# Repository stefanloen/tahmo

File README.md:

# realtime-gnssrefl
The repository for the water level measurement system from TAHMO.

The project contains the following parts

## analysis
Provides tools for analysing GNSS date (similar to what is in the firmware).

## control
Contains the firmware for the Pico 2. For installation ensure Rust is installed and use the following commands
```bash
$ cd control
$ rustup target add thumbv8m.main-none-eabihf
```
And flash and run the firmware with the following commands:
```bash
$ cd control
$ cargo run --release
```

Creating an uf2 file:
```bash
$ picotool uf2 convert .\target\thumbv8m.main-none-eabihf\release\control -t elf control.uf2
```
## docs
Webpage tools for flashing, configuring, data viewing and documentation. Hosted at Github: [TAHMO WLM Dashboard](https://stefanloen.github.io/tahmo/)

## hardware
Contains the KiCAD PCB design files as raw project folder and as archive. Also contains some design documentation.

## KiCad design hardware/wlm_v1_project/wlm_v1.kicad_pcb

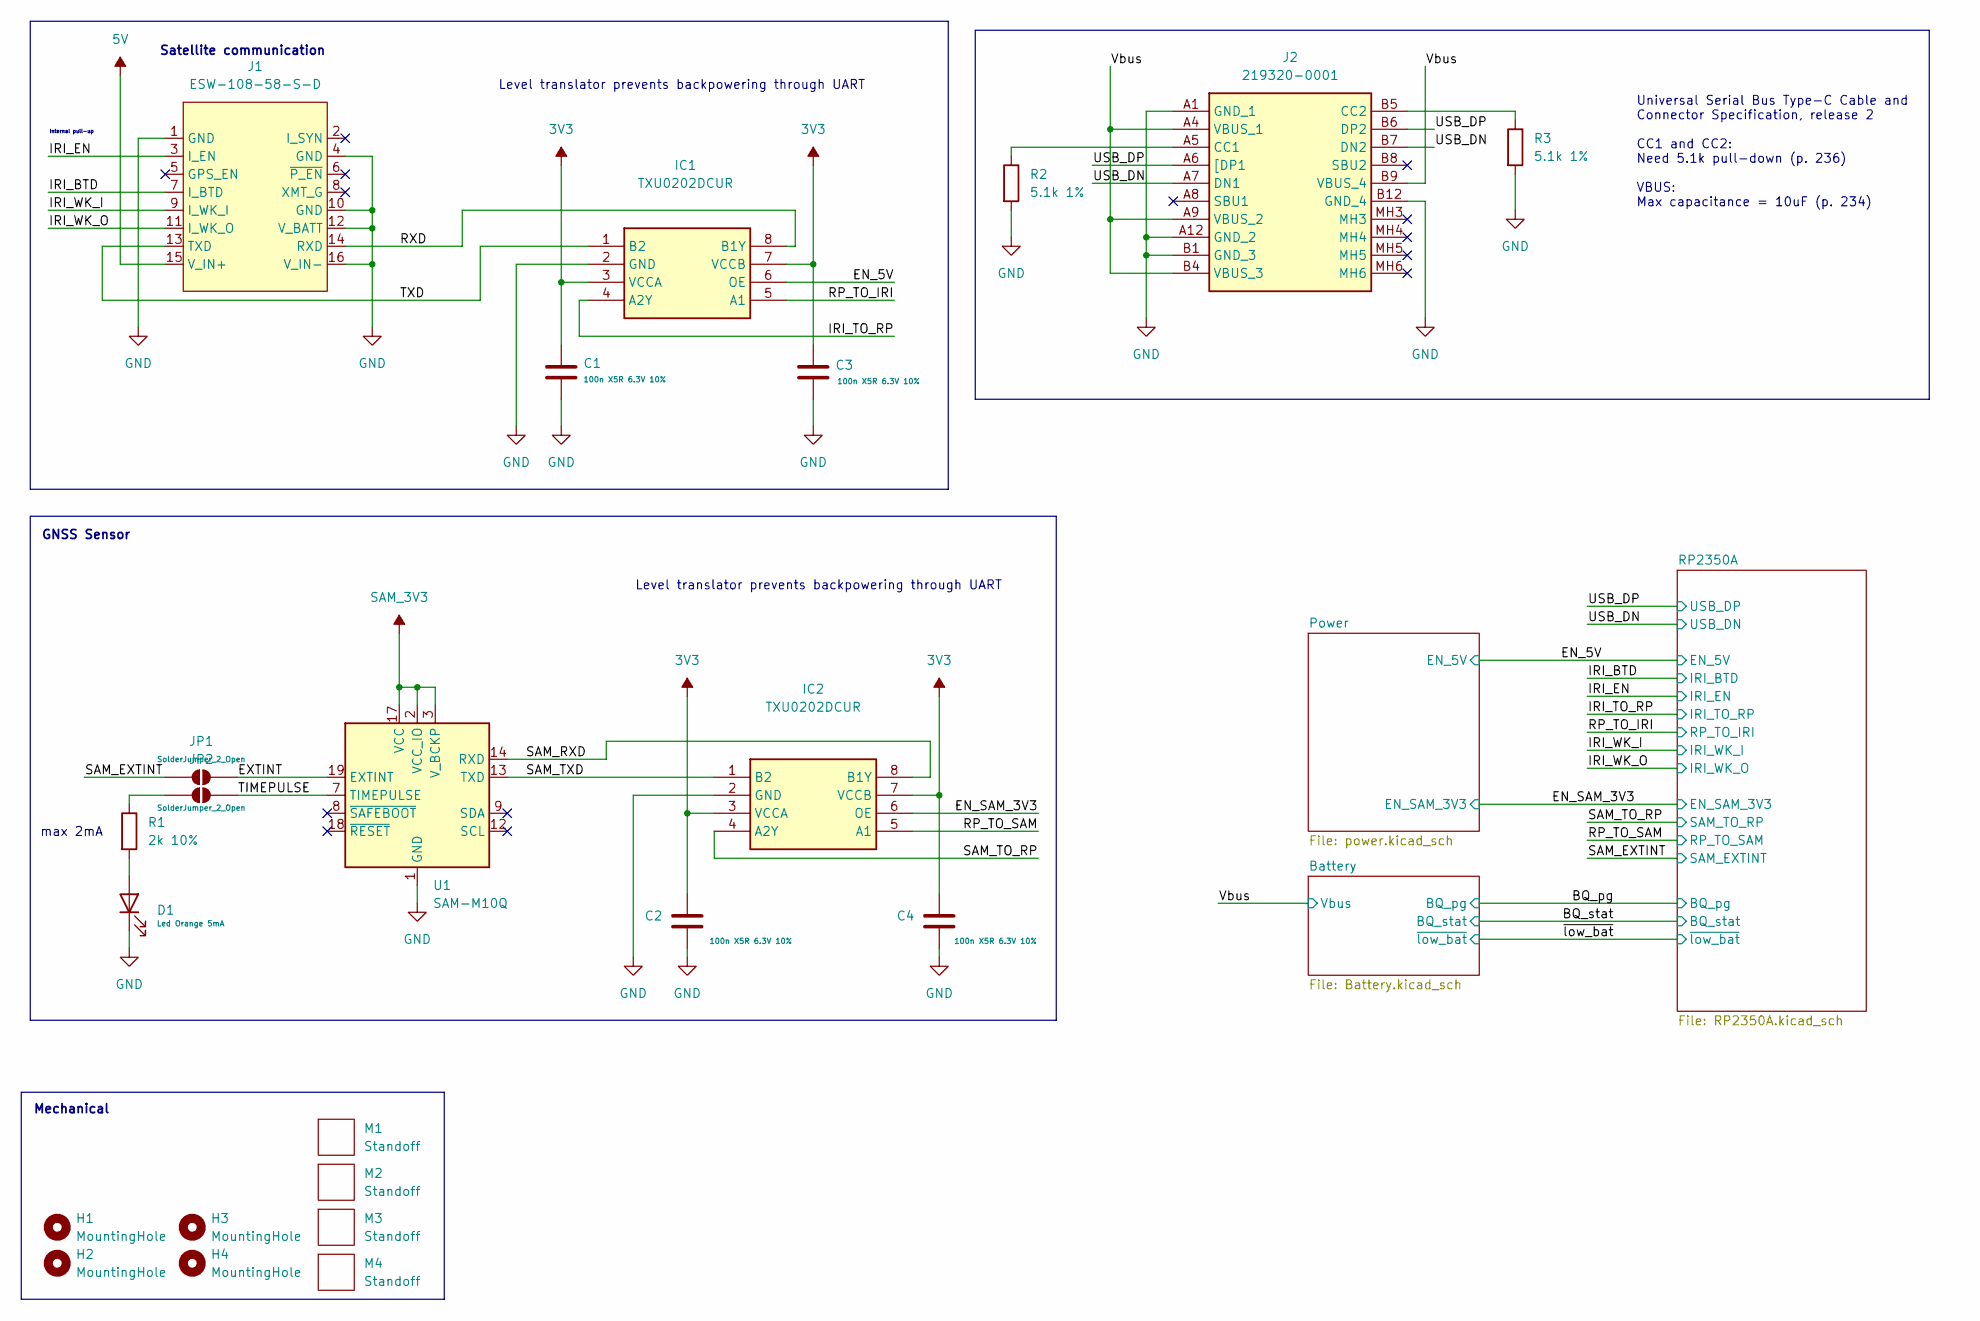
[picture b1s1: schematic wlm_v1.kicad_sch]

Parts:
C1, C2, C3, C4: 100n X5R 6.3V 10%; C_0603_1608Metric
D1: Led Orange 5mA; LED_0603_1608Metric
H1, H2, H3, H4: MountingHole; MountingHole_2.1mm
IC1, IC2: TXU0202DCUR; SOP50P310X90-8N; Mouser Part Number 595-TXU0202DCUR
J1: ESW-108-58-S-D; Rockblock_9704
J2: 219320-0001; 2193200001; Manufacturer_Part_Number 219320-0001; Mouser Part Number 538-219320-0001
JP1, JP2: SolderJumper_2_Open; SolderJumper-2_P1.3mm_Open_Pad1.0x1.5mm
M1, M2: Standoff; standoff_nohole
M3, M4: Standoff; standoff_hole
R1: 2k 10%; R_0603_1608Metric_Pad0.98x0.95mm_HandSolder
R2, R3: 5.1k 1%; R_0603_1608Metric_Pad0.98x0.95mm_HandSolder
U1: SAM-M10Q; ublox_SAM-M10Q

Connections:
3V3: C1.1, C2.1, C3.1, C4.1, IC1.3 (VCCA), IC1.7 (VCCB), IC2.3 (VCCA), IC2.7 (VCCB); also elsewhere on the board
5V: J1.15 (V_IN+); also elsewhere on the board
/EN_5V: IC1.6 (OE); also elsewhere on the board
/EN_SAM_3V3: IC2.6 (OE); also elsewhere on the board
/EXTINT: JP1.2 (B), U1.19 (EXTINT)
/IRI_BTD: J1.7 (I_BTD); also elsewhere on the board
/IRI_EN: J1.3 (I_EN); also elsewhere on the board
/IRI_TO_RP: IC1.4 (A2Y); also elsewhere on the board
/IRI_WK_I: J1.9 (I_WK_I); also elsewhere on the board
/IRI_WK_O: J1.11 (I_WK_O); also elsewhere on the board
/RP_TO_IRI: IC1.5 (A1); also elsewhere on the board
/RP_TO_SAM: IC2.5 (A1); also elsewhere on the board
/RXD: IC1.8 (B1Y), J1.14 (RXD)
/SAM_EXTINT: JP1.1 (A); also elsewhere on the board
/SAM_RXD: IC2.8 (B1Y), U1.14 (RXD)
/SAM_TO_RP: IC2.4 (A2Y); also elsewhere on the board
/SAM_TXD: IC2.1 (B2), U1.13 (TXD)
/TIMEPULSE: JP2.2 (B), U1.7 (TIMEPULSE)
/TXD: IC1.1 (B2), J1.13 (TXD)
/USB_DN: J2.A7 (DN1), J2.B7 (DN2); also elsewhere on the board
/USB_DP: J2.A6 ([DP1), J2.B6 (DP2); also elsewhere on the board
/Vbus: J2.A4 (VBUS_1), J2.A9 (VBUS_2), J2.B4 (VBUS_3), J2.B9 (VBUS_4); also elsewhere on the board
GND: C1.2, C2.2, C3.2, C4.2, D1.1 (K), IC1.2 (GND), IC2.2 (GND), J1.1 (GND), J1.4 (GND), J1.10 (GND), J1.12 (V_BATT), J1.16 (V_IN-), J2.A1 (GND_1), J2.A12 (GND_2), J2.B1 (GND_3), J2.B12 (GND_4), R2.2, R3.2, U1.1 (GND), U1.4 (GND), U1.5 (GND), U1.6 (GND), U1.10 (GND), U1.11 (GND), U1.15 (GND), U1.16 (GND), U1.20 (GND); also elsewhere on the board
unnamed: D1.2 (A), R1.2
unnamed: J2.A5 (CC1), R2.1
unnamed: J2.B5 (CC2), R3.1
unnamed: JP2.1 (A), R1.1
SAM_3V3: U1.2 (VCC_IO), U1.3 (V_BCKP), U1.17 (VCC); also elsewhere on the board

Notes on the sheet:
Internal pull-up
GNSS Sensor
Satellite communication
Mechanical
max 2mA
Universal Serial Bus Type-C Cable and Connector Specification, release 2 CC1 and CC2: Need 5.1k pull-down (p. 236) VBUS: Max capacitance = 10uF (p. 234)
Level translator prevents backpowering through UART
Level translator prevents backpowering through UART

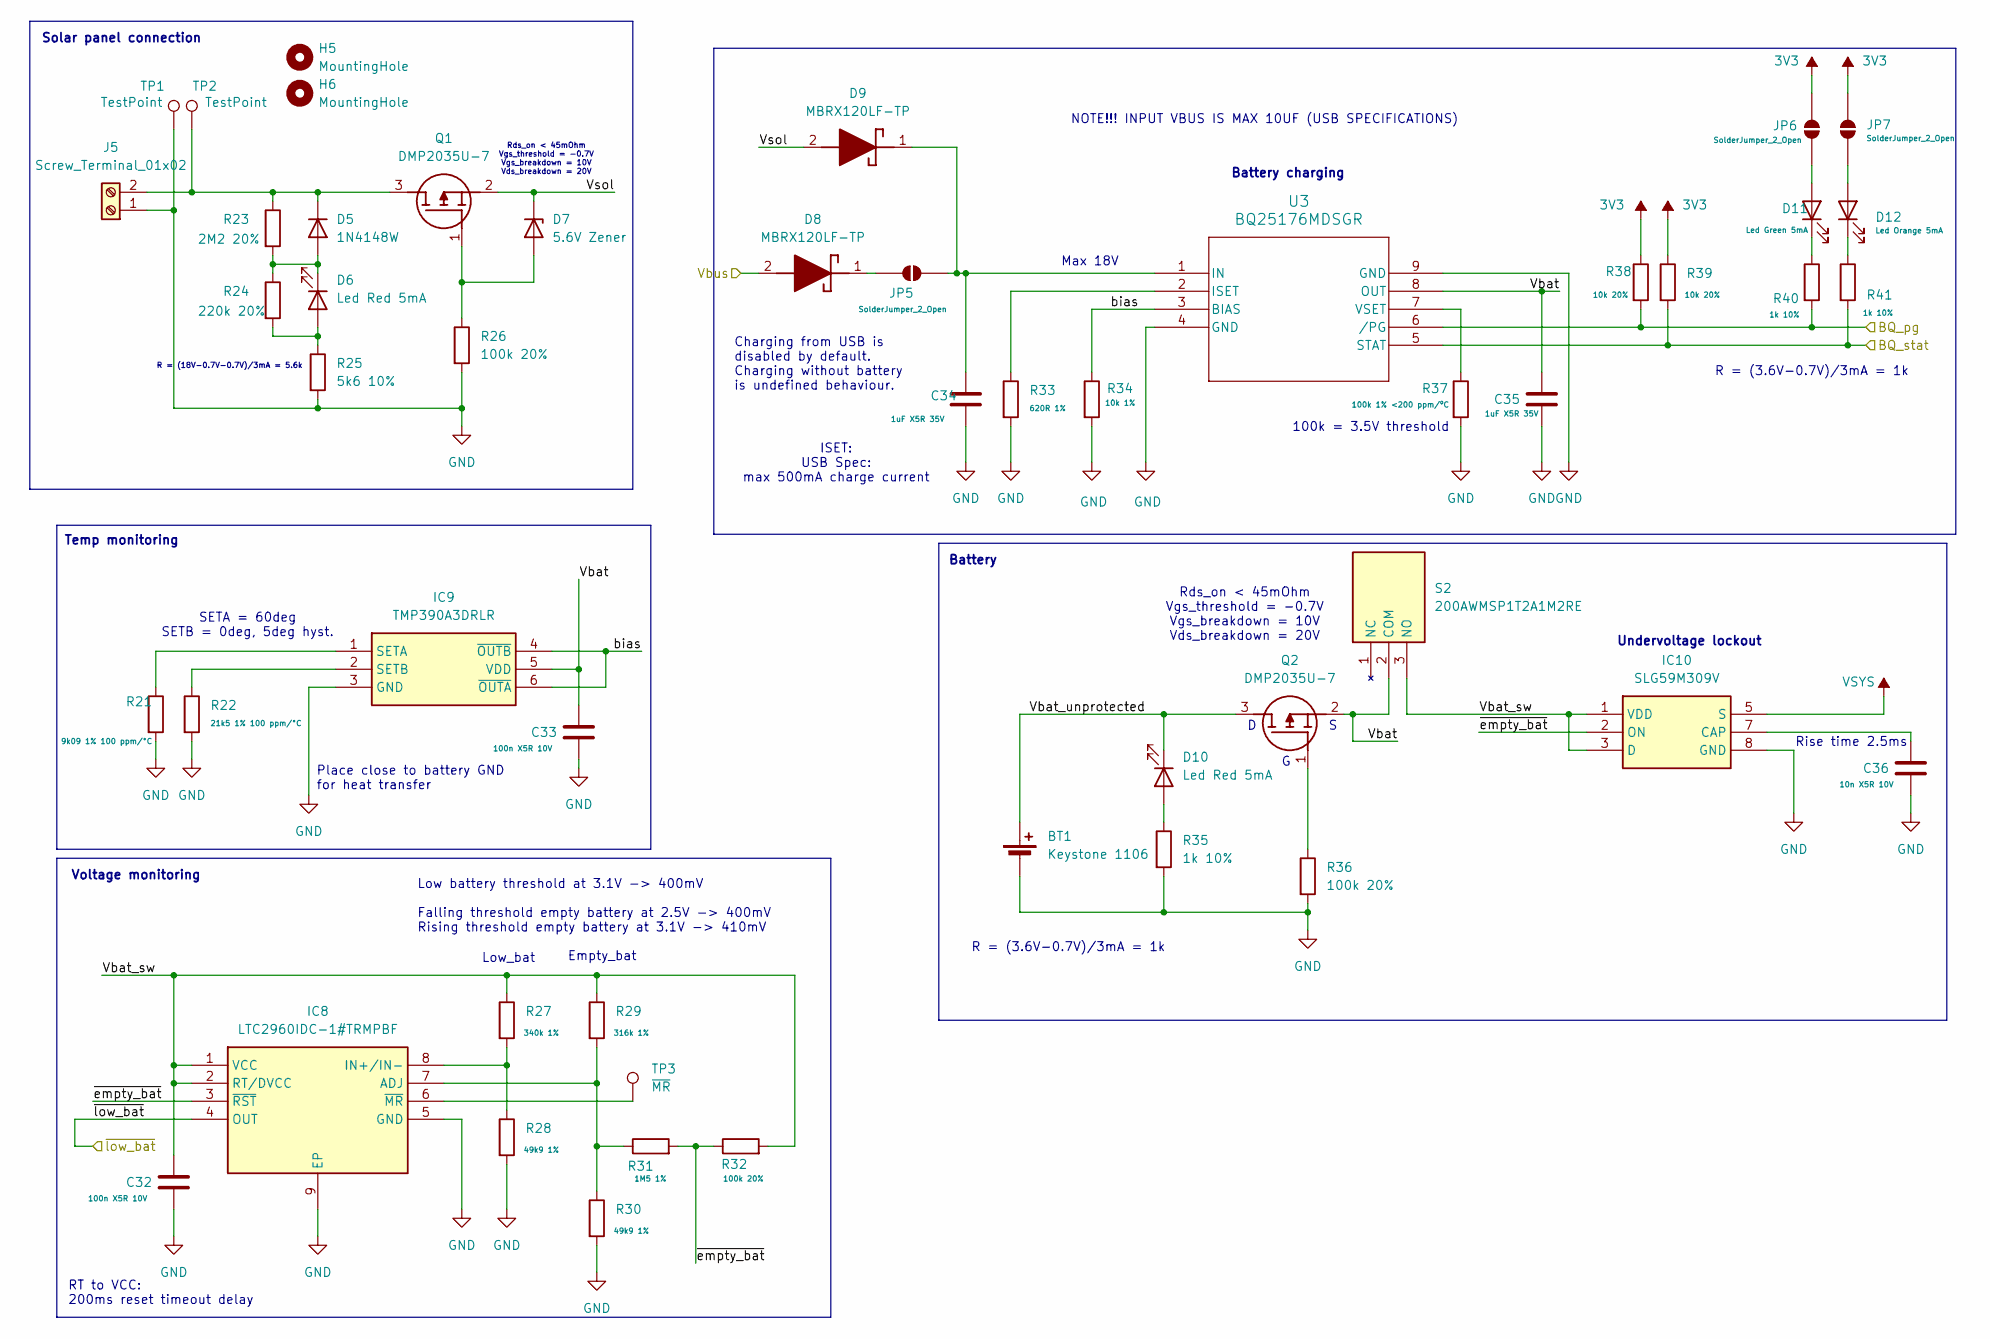
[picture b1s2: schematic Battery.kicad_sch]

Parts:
BT1: Keystone 1106; 26650_holder
C32, C33: 100n X5R 10V; C_0603_1608Metric
C34, C35: 1uF X5R 35V; C_0603_1608Metric
C36: 10n X5R 10V; C_0603_1608Metric
D5: 1N4148W; D_SOD-123
D6, D10: Led Red 5mA; LED_0603_1608Metric
D7: 5.6V Zener; D_SOD-123
D8, D9: MBRX120LF-TP; SOD3716X135N; Mouser Part Number 833-MBRX120LF-TP
D11: Led Green 5mA; LED_0603_1608Metric
D12: Led Orange 5mA; LED_0603_1608Metric
H5, H6: MountingHole; MountingHole_3.2mm_M3
IC8: LTC2960IDC-1#TRMPBF; SON45P200X200X80-9N-D; Mouser Part Number 584-C2960IDC-3TRMPBF
IC9: TMP390A3DRLR; SOTFL50P160X60-6N; Mouser Part Number 595-TMP390A3DRLR
IC10: SLG59M309V; Mouser Part Number 402-SLG59M309V
J5: Screw_Terminal_01x02; TerminalBlock_Phoenix_MKDS-1,5-2-5.08_1x02_P5.08mm_Horizont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
JP5, JP6, JP7: SolderJumper_2_Open; SolderJumper-2_P1.3mm_Open_Pad1.0x1.5mm
Q1, Q2: DMP2035U-7; DMP2035U7; Mouser Part Number 621-DMP2035U-7
R21: 9k09 1% 100 ppm/°C; R_0603_1608Metric_Pad0.98x0.95mm_HandSolder
R22: 21k5 1% 100 ppm/°C; R_0603_1608Metric_Pad0.98x0.95mm_HandSolder
R23: 2M2 20%; R_0603_1608Metric_Pad0.98x0.95mm_HandSolder
R24: 220k 20%; R_0603_1608Metric_Pad0.98x0.95mm_HandSolder
R25: 5k6 10%; R_0603_1608Metric_Pad0.98x0.95mm_HandSolder
R26, R32, R36: 100k 20%; R_0603_1608Metric_Pad0.98x0.95mm_HandSolder
R27: 340k 1%; R_0603_1608Metric_Pad0.98x0.95mm_HandSolder
R28, R30: 49k9 1%; R_0603_1608Metric_Pad0.98x0.95mm_HandSolder
R29: 316k 1%; R_0603_1608Metric_Pad0.98x0.95mm_HandSolder
R31: 1M5 1%; R_0603_1608Metric_Pad0.98x0.95mm_HandSolder
R33: 620R 1%; R_0603_1608Metric_Pad0.98x0.95mm_HandSolder
R34: 10k 1%; R_0603_1608Metric_Pad0.98x0.95mm_HandSolder
R35, R40, R41: 1k 10%; R_0603_1608Metric_Pad0.98x0.95mm_HandSolder
R37: 100k 1% <200 ppm/ºC; R_0603_1608Metric_Pad0.98x0.95mm_HandSolder
R38, R39: 10k 20%; R_0603_1608Metric_Pad0.98x0.95mm_HandSolder
S2: 200AWMSP1T2A1M2RE; Mouser Part Number 612-200A-A2162
TP1, TP2: TestPoint; TestPoint_THTPad_D2.0mm_Drill1.0mm
TP3: ~{MR}; TestPoint_Pad_D3.0mm
U3: BQ25176MDSGR; WSON_MDSGR_TEX

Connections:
3V3: JP6.2 (B), JP7.2 (B), R38.1, R39.1; also elsewhere on the board
/BQ_pg: R38.2, R40.2, U3.6 (/PG); also elsewhere on the board
/BQ_stat: R39.2, R41.2, U3.5 (STAT); also elsewhere on the board
/Battery/Vbat: C33.1, C35.1, IC9.5 (VDD), Q2.2 (S), S2.2 (COM), U3.8 (OUT)
/Battery/Vbat_sw: C32.1, IC8.1 (VCC), IC8.2 (RT/DVCC), IC10.1 (VDD), IC10.3 (D), R27.1, R29.1, R32.2, S2.3 (NO)
/Battery/Vbat_unprotected: BT1.1 (+), D10.1 (K), Q2.3 (D)
/Battery/Vsol: D7.1 (K), D9.2 (A), Q1.2 (S)
/Battery/bias: IC9.4 (~OUTB), IC9.6 (~OUTA), R34.1, U3.3 (BIAS)
/Battery/~empty_bat: IC8.3 (~RST), IC10.2 (ON), R31.2, R32.1
/Vbus: D8.2 (A); also elsewhere on the board
/~low_bat: IC8.4 (OUT); also elsewhere on the board
GND: BT1.2 (-), C32.2, C33.2, C34.2, C35.2, C36.2, IC8.5 (GND), IC8.9 (EP), IC9.3 (GND), IC10.8 (GND), J5.1, R21.2, R22.2, R25.2, R26.2, R28.2, R30.2, R33.2, R34.2, R35.2, R36.2, R37.2, TP1.1 (1_1), U3.4 (GND), U3.9 (GND); also elsewhere on the board
unnamed: D5.2 (A), D6.1 (K), R23.2, R24.1
unnamed: D5.1 (K), J5.2, Q1.3 (D), R23.1, TP2.1 (1_1)
unnamed: D6.2 (A), R24.2, R25.1
unnamed: D7.2 (A), Q1.1 (G), R26.1
unnamed: D8.1 (K), JP5.2 (B)
unnamed: C34.1, D9.1 (K), JP5.1 (A), U3.1 (IN)
unnamed: D10.2 (A), R35.1
unnamed: D11.2 (A), JP6.1 (A)
unnamed: D11.1 (K), R40.1
unnamed: D12.2 (A), JP7.1 (A)
unnamed: D12.1 (K), R41.1
unnamed: IC8.7 (ADJ), R29.2, R30.1, R31.1
unnamed: IC8.8 (IN+/IN-), R27.2, R28.1
unnamed: IC8.6 (~MR), TP3.1 (1_1)
unnamed: IC9.1 (SETA), R21.1
unnamed: IC9.2 (SETB), R22.1
unnamed: C36.1, IC10.7 (CAP)
unnamed: Q2.1 (G), R36.1
unnamed: R33.1, U3.2 (ISET)
unnamed: R37.1, U3.7 (VSET)
VSYS: IC10.5 (S); also elsewhere on the board

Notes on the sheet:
Voltage monitoring
Battery
Empty_bat
SETA = 60deg SETB = 0deg, 5deg hyst.
Place close to battery GND for heat transfer
ISET: USB Spec: max 500mA charge current
Max 18V
Rds_on < 45mOhm Vgs_threshold = -0.7V Vgs_breakdown = 10V Vds_breakdown = 20V
RT to VCC: 200ms reset timeout delay
R = (18V-0.7V-0.7V)/3mA = 5.6k
R = (3.6V-0.7V)/3mA = 1k
Temp monitoring
100k = 3.5V threshold
Solar panel connection
Low battery threshold at 3.1V -> 400mV Falling threshold empty battery at 2.5V -> 400mV Rising threshold empty battery at 3.1V -> 410mV
Charging from USB is disabled by default. Charging without battery is undefined behaviour.
Battery charging
Low_bat
Undervoltage lockout
Rise time 2.5ms
NOTE!!! INPUT VBUS IS MAX 10UF (USB SPECIFICATIONS)

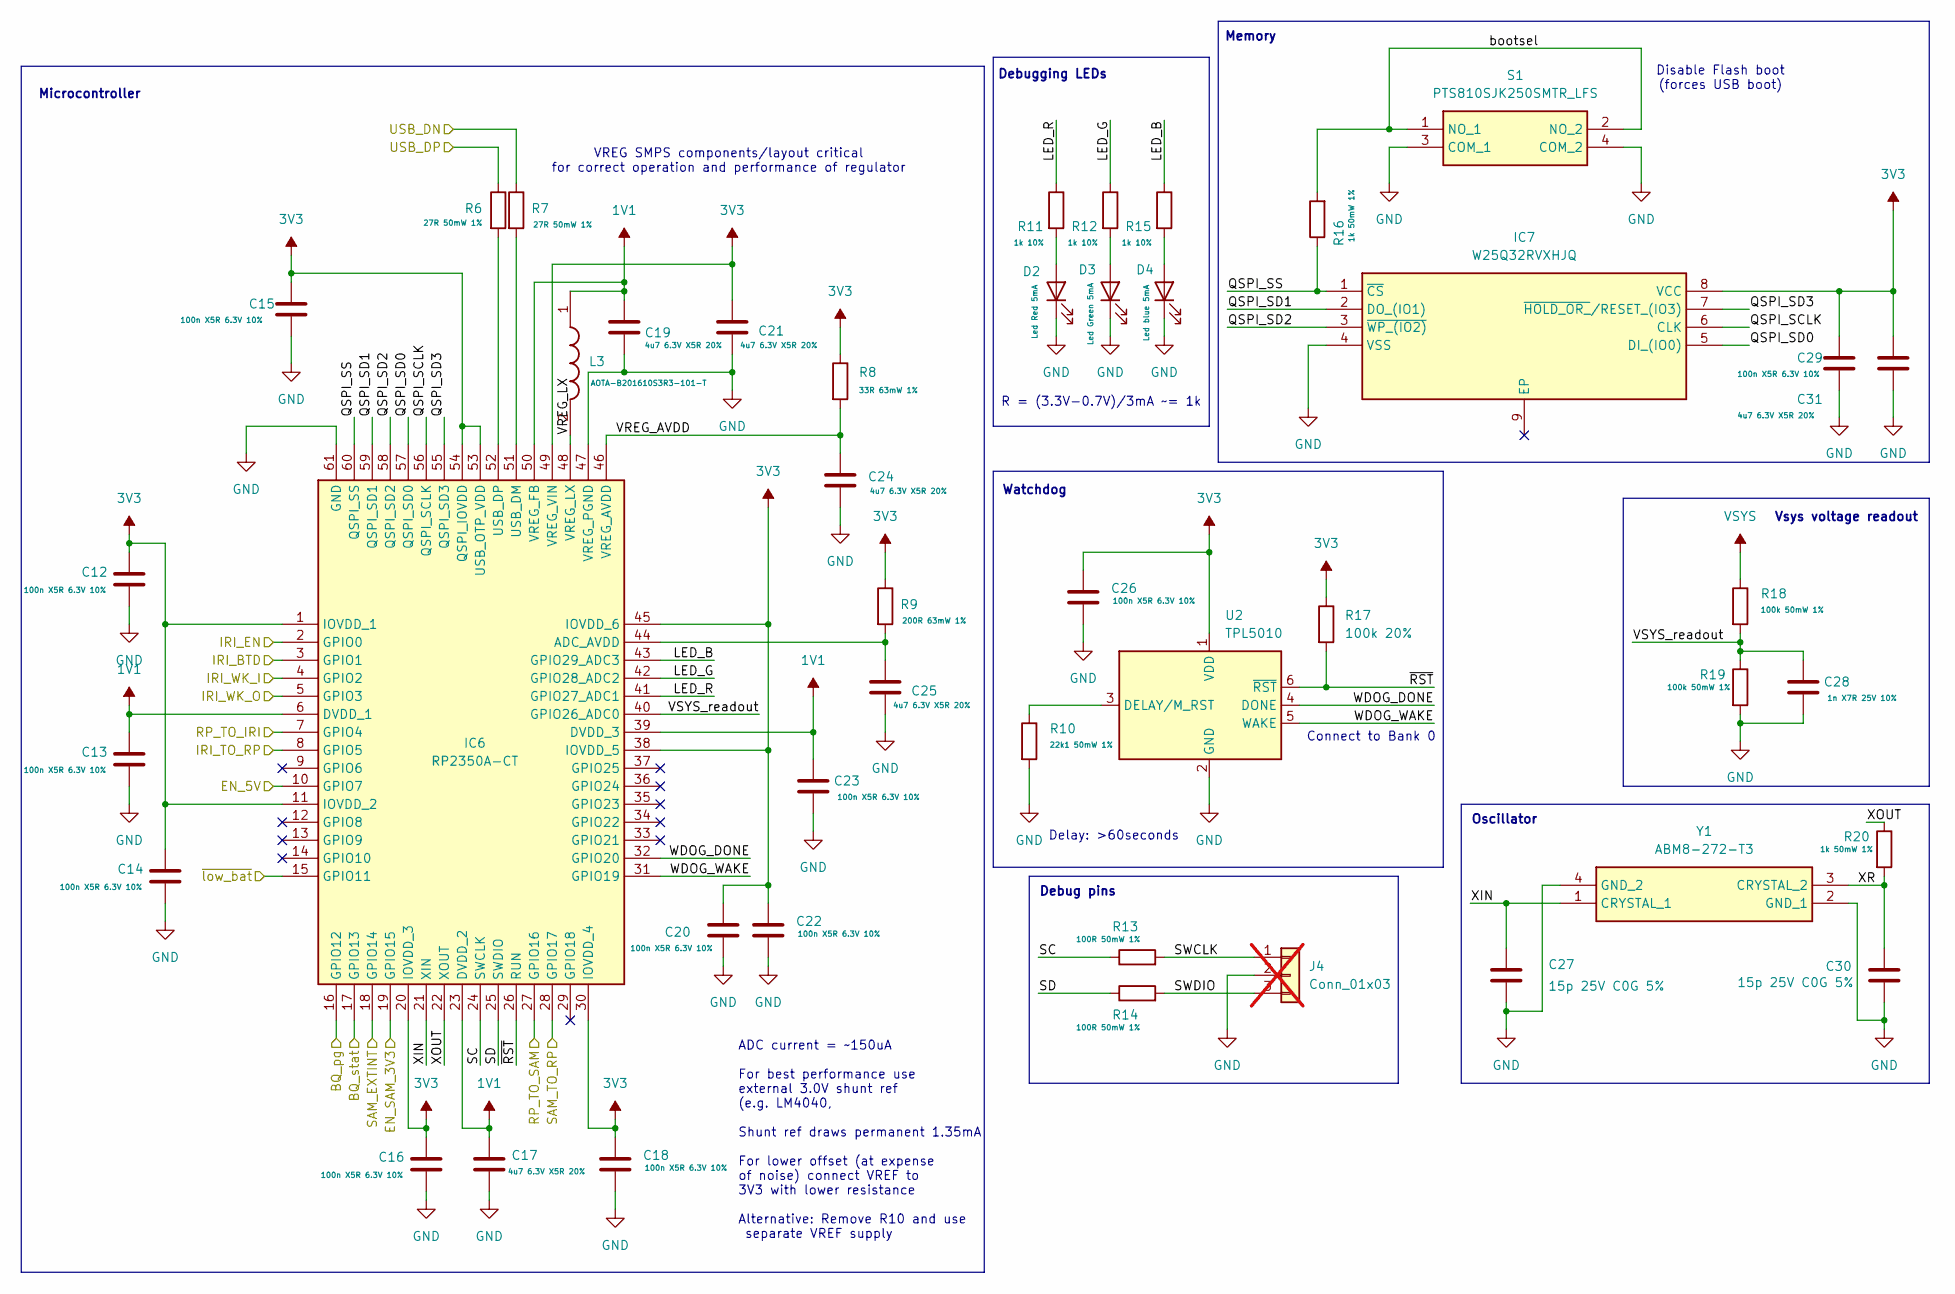
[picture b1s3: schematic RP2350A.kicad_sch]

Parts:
C12, C13, C14, C15, C16, C18, C20, C22, C23, C26, C29: 100n X5R 6.3V 10%; C_0603_1608Metric
C17, C25, C31: 4u7 6.3V X5R 20%; C_0603_1608Metric
C19, C21, C24: 4u7 6.3V X5R 20%; C_0402_1005Metric
C27, C30: 15p 25V C0G 5%; C_0603_1608Metric
C28: 1n X7R 25V 10%; C_0603_1608Metric
D2: Led Red 5mA; LED_0603_1608Metric
D3: Led Green 5mA; LED_0603_1608Metric
D4: Led blue 5mA; LED_0603_1608Metric
IC6: RP2350A-CT; QFN40P700X700X90-61N-D; Manufacturer_Part_Number RP2350A-CT
IC7: W25Q32RVXHJQ; SON50P300X200X40-9N; Manufacturer_Part_Number W25Q32RVXHJQ
J4: Conn_01x03; PinHeader_1x03_P2.54mm_Vertical; not fitted
L3: AOTA-B201610S3R3-101-T; AOTAB201610S3R3101T; Mouser Part Number 815-AB201610S3R3101T
R6, R7: 27R 50mW 1%; R_0603_1608Metric_Pad0.98x0.95mm_HandSolder
R8: 33R 63mW 1%; R_0402_1005Metric_Pad0.72x0.64mm_HandSolder
R9: 200R 63mW 1%; R_0603_1608Metric_Pad0.98x0.95mm_HandSolder
R10: 22k1 50mW 1%; R_0603_1608Metric_Pad0.98x0.95mm_HandSolder
R11, R12, R15: 1k 10%; R_0603_1608Metric_Pad0.98x0.95mm_HandSolder
R13, R14: 100R 50mW 1%; R_0603_1608Metric_Pad0.98x0.95mm_HandSolder
R16, R20: 1k 50mW 1%; R_0603_1608Metric_Pad0.98x0.95mm_HandSolder
R17: 100k 20%; R_0603_1608Metric_Pad0.98x0.95mm_HandSolder
R18, R19: 100k 50mW 1%; R_0603_1608Metric_Pad0.98x0.95mm_HandSolder
S1: PTS810SJK250SMTR_LFS; PTS810SJK250SMTRLFS; Mouser Part Number 611-PTS810SJK250SMTR
U2: TPL5010; SOT-23-6
Y1: ABM8-272-T3; ABM8272T3; Mouser Part Number 815-ABM8-272-T3

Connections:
1V1: C13.1, C17.1, C19.1, C23.1, IC6.6 (DVDD_1), IC6.23 (DVDD_2), IC6.39 (DVDD_3), IC6.50 (VREG_FB), L3.1
3V3: C12.1, C14.1, C15.1, C16.1, C18.1, C20.1, C21.1, C22.1, C26.1, C29.1, C31.1, IC6.1 (IOVDD_1), IC6.11 (IOVDD_2), IC6.20 (IOVDD_3), IC6.30 (IOVDD_4), IC6.38 (IOVDD_5), IC6.45 (IOVDD_6), IC6.49 (VREG_VIN), IC6.53 (USB_OTP_VDD), IC6.54 (QSPI_IOVDD), IC7.8 (VCC), R8.1, R9.1, R17.1, U2.1 (VDD); also elsewhere on the board
/BQ_pg: IC6.16 (GPIO12); also elsewhere on the board
/BQ_stat: IC6.17 (GPIO13); also elsewhere on the board
/EN_5V: IC6.10 (GPIO7); also elsewhere on the board
/EN_SAM_3V3: IC6.19 (GPIO15); also elsewhere on the board
/IRI_BTD: IC6.3 (GPIO1); also elsewhere on the board
/IRI_EN: IC6.2 (GPIO0); also elsewhere on the board
/IRI_TO_RP: IC6.8 (GPIO5); also elsewhere on the board
/IRI_WK_I: IC6.4 (GPIO2); also elsewhere on the board
/IRI_WK_O: IC6.5 (GPIO3); also elsewhere on the board
/RP2350A/LED_B: IC6.43 (GPIO29_ADC3), R15.1
/RP2350A/LED_G: IC6.42 (GPIO28_ADC2), R12.1
/RP2350A/LED_R: IC6.41 (GPIO27_ADC1), R11.1
/RP2350A/QSPI_SCLK: IC6.56 (QSPI_SCLK), IC7.6 (CLK)
/RP2350A/QSPI_SD0: IC6.57 (QSPI_SD0), IC7.5 (DI_(IO0))
/RP2350A/QSPI_SD1: IC6.59 (QSPI_SD1), IC7.2 (DO_(IO1))
/RP2350A/QSPI_SD2: IC6.58 (QSPI_SD2), IC7.3 (~WP_(IO2))
/RP2350A/QSPI_SD3: IC6.55 (QSPI_SD3), IC7.7 (~HOLD_OR_/RESET_(IO3))
/RP2350A/QSPI_SS: IC6.60 (QSPI_SS), IC7.1 (~CS), R16.1
/RP2350A/SC: IC6.24 (SWCLK), R13.1
/RP2350A/SD: IC6.25 (SWDIO), R14.1
/RP2350A/SWCLK: J4.1, R13.2
/RP2350A/SWDIO: J4.3, R14.2
/RP2350A/VREG_AVDD: C24.1, IC6.46 (VREG_AVDD), R8.2
/RP2350A/VREG_LX: IC6.48 (VREG_LX), L3.2
/RP2350A/VSYS_readout: C28.1, IC6.40 (GPIO26_ADC0), R18.2, R19.1
/RP2350A/WDOG_DONE: IC6.32 (GPIO20), U2.4 (DONE)
/RP2350A/WDOG_WAKE: IC6.31 (GPIO19), U2.5 (WAKE)
/RP2350A/XIN: C27.1, IC6.21 (XIN), Y1.1 (CRYSTAL_1)
/RP2350A/XOUT: IC6.22 (XOUT), R20.1
/RP2350A/XR: C30.1, R20.2, Y1.3 (CRYSTAL_2)
/RP2350A/bootsel: R16.2, S1.1 (NO_1), S1.2 (NO_2)
/RP2350A/~RST: IC6.26 (RUN), R17.2, U2.6 (~RST)
/RP_TO_IRI: IC6.7 (GPIO4); also elsewhere on the board
/RP_TO_SAM: IC6.27 (GPIO16); also elsewhere on the board
/SAM_EXTINT: IC6.18 (GPIO14); also elsewhere on the board
/SAM_TO_RP: IC6.28 (GPIO17); also elsewhere on the board
/USB_DN: R7.1; also elsewhere on the board
/USB_DP: R6.1; also elsewhere on the board
/~low_bat: IC6.15 (GPIO11); also elsewhere on the board
GND: C12.2, C13.2, C14.2, C15.2, C16.2, C17.2, C18.2, C19.2, C20.2, C21.2, C22.2, C23.2, C24.2, C25.2, C26.2, C27.2, C28.2, C29.2, C30.2, C31.2, D2.1 (K), D3.1 (K), D4.1 (K), IC6.47 (VREG_PGND), IC6.61 (GND), IC7.4 (VSS), J4.2, R10.2, R19.2, S1.3 (COM_1), S1.4 (COM_2), U2.2 (GND), Y1.2 (GND_1), Y1.4 (GND_2); also elsewhere on the board
unnamed: D2.2 (A), R11.2
unnamed: D3.2 (A), R12.2
unnamed: D4.2 (A), R15.2
unnamed: C25.1, IC6.44 (ADC_AVDD), R9.2
unnamed: IC6.51 (USB_DM), R7.2
unnamed: IC6.52 (USB_DP), R6.2
unnamed: R10.1, U2.3 (DELAY/M_RST)
VSYS: R18.1; also elsewhere on the board

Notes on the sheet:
Delay: >60seconds
Watchdog
Disable Flash boot (forces USB boot)
Vsys voltage readout
Debug pins
Debugging LEDs
VREG SMPS components/layout critical for correct operation and performance of regulator
Microcontroller
Memory
Oscillator
ADC current = ~150uA For best performance use external 3.0V shunt ref (e.g. LM4040, Shunt ref draws permanent 1.35mA For lower offset (at expense of noise) connect VREF to 3V3 with lower resistance Alternative: Remove R10 and use separate VREF supply
Connect to Bank 0
R = (3.3V-0.7V)/3mA ~= 1k

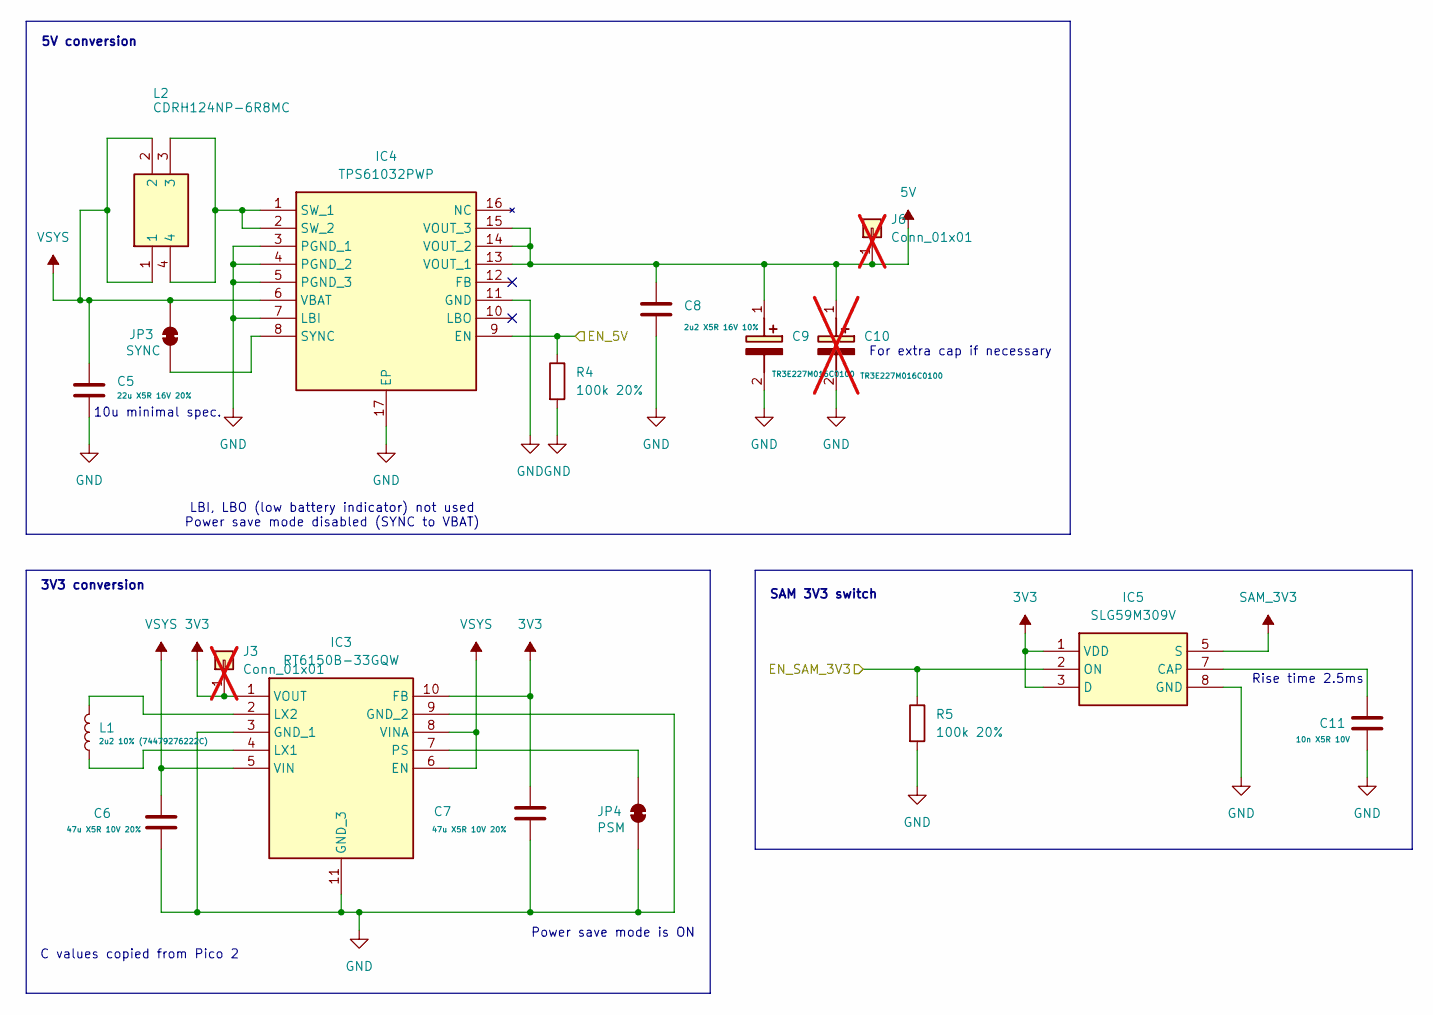
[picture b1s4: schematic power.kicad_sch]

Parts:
C5: 22u X5R 16V 20%; C_0805_2012Metric
C6, C7: 47u X5R 10V 20%; C_1210_3225Metric
C8: 2u2 X5R 16V 10%; C_0805_2012Metric
C9: TR3E227M016C0100; CAPPM7343X430N; Mouser Part Number 74-TR3E227M016C0100
C10: TR3E227M016C0100; CAPPM7343X430N; Mouser Part Number 74-TR3E227M016C0100; not fitted
C11: 10n X5R 10V; C_0603_1608Metric
IC3: RT6150B-33GQW; SON50P250X250X80-11N-D; Mouser Part Number 835-RT6150B-33GQW
IC4: TPS61032PWP; SOP65P640X120-17N; Mouser Part Number 595-TPS61032PWPR
IC5: SLG59M309V; Mouser Part Number 402-SLG59M309V
J3, J6: Conn_01x01; PinHeader_1x01_P2.54mm_Vertical; not fitted
JP3: SYNC; SolderJumper-2_P1.3mm_Bridged_Pad1.0x1.5mm
JP4: PSM; SolderJumper-2_P1.3mm_Bridged_Pad1.0x1.5mm
L1: 2u2 10% (74479276222C); L_Wuerth_PMFI-201610
L2: CDRH124NP-6R8MC; Mouser Part Number 851-CDRH124NP-6R8MC
R4, R5: 100k 20%; R_0603_1608Metric_Pad0.98x0.95mm_HandSolder

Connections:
3V3: C7.1, IC3.1 (VOUT), IC3.10 (FB), IC5.1 (VDD), IC5.3 (D), J3.1 (Pin_1_1); also elsewhere on the board
5V: C8.1, C9.1 (+), C10.1 (+), IC4.13 (VOUT_1), IC4.14 (VOUT_2), IC4.15 (VOUT_3), J6.1 (Pin_1_1); also elsewhere on the board
/EN_5V: IC4.9 (EN), R4.1; also elsewhere on the board
/EN_SAM_3V3: IC5.2 (ON), R5.1; also elsewhere on the board
GND: C5.2, C6.2, C7.2, C8.2, C9.2 (-), C10.2 (-), C11.2, IC3.3 (GND_1), IC3.9 (GND_2), IC3.11 (GND_3), IC4.3 (PGND_1), IC4.4 (PGND_2), IC4.5 (PGND_3), IC4.7 (LBI), IC4.11 (GND), IC4.17 (EP), IC5.8 (GND), JP4.2 (B), R4.2, R5.2; also elsewhere on the board
unnamed: IC3.4 (LX1), L1.1
unnamed: IC3.2 (LX2), L1.2
unnamed: IC3.7 (PS), JP4.1 (A)
unnamed: IC4.1 (SW_1), IC4.2 (SW_2), L2.3, L2.4
unnamed: IC4.8 (SYNC), JP3.2 (B)
unnamed: C11.1, IC5.7 (CAP)
SAM_3V3: IC5.5 (S); also elsewhere on the board
VSYS: C5.1, C6.1, IC3.5 (VIN), IC3.6 (EN), IC3.8 (VINA), IC4.6 (VBAT), JP3.1 (A), L2.1, L2.2; also elsewhere on the board

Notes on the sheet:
LBI, LBO (low battery indicator) not used Power save mode disabled (SYNC to VBAT)
5V conversion
3V3 conversion
SAM 3V3 switch
Rise time 2.5ms
10u minimal spec.
Power save mode is ON
C values copied from Pico 2
For extra cap if necessary
